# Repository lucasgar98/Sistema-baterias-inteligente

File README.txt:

================================================================================
  SISTEMA INTELIGENTE DE CARGA, DESCARGA Y DIAGNÓSTICO DE BATERÍAS (PROYECTO)
================================================================================

Este proyecto es una plataforma integrada de hardware y software diseñada para 
realizar ciclos de carga, descarga y caracterización de baterías de múltiples 
químicas (Li-Ion, Pb, NiMH). 

El sistema combina el control de potencia en tiempo real (MicroPython), una 
interfaz táctil física (LVGL v8 en CYD), visión por computadora para 
identificación de baterías (ESP32-CAM + pyzbar) y un backend de monitoreo y 
almacenamiento (FastAPI + SQLite + InfluxDB + MQTT) orquestado en Docker.

--------------------------------------------------------------------------------
1. ARQUITECTURA GENERAL Y FLUJO DE DATOS
--------------------------------------------------------------------------------

El flujo de información y control entre los componentes se organiza así:

   [ ESP32-CAM ] -------------( WiFi: Stream MJPEG )-------------> [ FASTAPI ]
         |                                                            |
     ( UART1 )                                                   ( Escribe a DB )
         |                                                            |
         v                                                            v
  [ ESP32 MASTER ]                                            [ SQLITE / INFLUX ]
    |          |
 ( UART2 )   ( I2C / PWM / ADC )
    |          |
    v          v
 [ CYD ]     [ SENSORES (INA219/NTC) y MOSFETS DE POTENCIA ]
 
* Comunicaciones clave:
  - ESP32 Master <-> Cheap Yellow Display (CYD): UART2 a 115200 baudios.
  - ESP32 Master <-> ESP32-CAM: UART1 a 115200 baudios.
  - ESP32 Master -> Sensor de Corriente (INA219): Bus I2C.
  - ESP32 Master -> MOSFETs de potencia: Señal digital PWM.
  - FastAPI (Servidor) <-> Broker MQTT (Mosquitto): Red local TCP.

--------------------------------------------------------------------------------
2. ESTRUCTURA DEL PROYECTO (Workspace)
--------------------------------------------------------------------------------

El repositorio se organiza de la siguiente manera:

/ (Raíz del proyecto)
|-- docker-compose.yml           <- Orquestador de servicios (Mosquitto, InfluxDB, API)
|-- README.txt                   <- Esta documentación principal
|
|-- backend/                     <- Servidor backend y panel de control web
|   |-- main.py                  <- API FastAPI, cliente MQTT, base de datos y lector QR
|   |-- dockerfile               <- Archivo de construcción de imagen Docker
|   |-- baterias.db              <- Base de datos SQLite (se genera sola al arrancar)
|   `-- frontend/                <- Código del dashboard web para PC
|       `-- index.html           <- Panel de monitoreo web interactivo
|
|-- firmware/                    <- Código fuente para los microcontroladores
|   |-- esp32_master/            <- Firmware del ESP32 Principal (MicroPython)
|   |   |-- main.py              # Lógica de potencia, control PWM y lectura de sensores
|   |   |-- config.json.template # Plantilla para configurar datos de red local
|   |   `-- legacy/              # Histórico: código viejo con botones analógicos
|   |       `-- legacy_main_buttons.py
|   |-- pantalla_cyd/            <- Interfaz gráfica táctil (ESP32 CYD con Arduino C++)
|   |   |-- pantalla_cyd.ino     # Inicialización, drivers de pantalla y lazo táctil
|   |   |-- ui.cpp               # Creación manual de pantallas, sliders y callbacks
|   |   `-- ui.h                 # Definición de variables de pantalla
|   |-- espcam/                  <- Cámara de lectura QR (ESP32-CAM con Arduino C++)
|   |   |-- espcam.ino           # Servidor web local de streaming MJPEG
|   |   `-- legacy/              # Histórico: lector de QR local serial
|   |       `-- legacy_serial_qr_reader.txt
|   `-- test_pantalla/           <- Diagnóstico de hardware táctil y colores
|       `-- test_pantalla.ino
|
|-- hardware/                    <- Archivos de diseño físico y circuital
|   |-- pcb_cargador/            <- Proyecto completo de la placa en KiCad
|   |-- ui_design/               <- Proyecto de prototipado original en EEZ Studio
|   |   |-- Lector Bateria.eez-project
|   |   `-- src/                 # Código LVGL exportado originalmente por EEZ
|   `-- 3d_print/                <- Modelos 3D de la carcasa (.3mf)
|
`-- documentacion/               <- Archivos de soporte y estudio
    |-- datasheets/              <- Fichas técnicas en PDF (MOSFETs, integrados)
    |-- BOM/                     <- Listas de materiales (formatos Excel y Word)
    |-- informes/                <- Reportes académicos y bitácora de cambios (PDF)
    `-- videos/                  <- Videos de demostración del circuito (MP4)

--------------------------------------------------------------------------------
3. EXPLICACIÓN DE COMPONENTES
--------------------------------------------------------------------------------

[ ESP32 Master ]
* Lazo de Corriente Constante: Genera PWM a 500 Hz para excitar los gates de los 
  MOSFETs. Aumenta o disminuye el ciclo de trabajo (+/- 20 pasos sobre 1000) 
  dependiendo de si la lectura de corriente está por debajo o por encima del 
  objetivo deseado (ej. 900 mA).
* Corrección de Tensión: Compensa dinámicamente las lecturas del voltaje en 
  función de la caída de tensión introducida por shunts y cables durante la 
  carga (-0.0001V por mA) y descarga (+0.00015V por mA).
* Filtro de Temperatura (EMA): Suaviza las muestras analógicas del NTC usando
  un promedio móvil exponencial con factor alpha = 0.08:
     T_filtrada = 0.08 * T_actual + 0.92 * T_anterior
* Seguridad Térmica: Si la temperatura supera los 45°C, detiene de inmediato 
  las salidas PWM y bloquea la operación. Se restablece automáticamente cuando 
  desciende por debajo de los 40°C.
* Lógica AUTO (Máquina de Estados): Corre la secuencia:
  Descarga inicial -> Espera enfriamiento -> Carga -> Espera -> Descarga de test.

[ Pantalla CYD (Cheap Yellow Display) ]
* Interfaz LVGL v8: Cuenta con navegación deslizable por pestañas (TileView):
  1. Principal: Mediciones en vivo, botones de acción rápida, QR activo.
  2. Parámetros: Selección de químicas y límites de voltaje/corriente.
  3. Red: Conexión WiFi/MQTT on-demand y teclado virtual para configuración.
* Integración UART: La pantalla no toma decisiones de potencia; le envía comandos 
  al Master (ej: "START_C", "SET_LIMITS:c,d,i") y recibe de éste cadenas JSON 
  con la telemetría en tiempo real.

[ ESP32-CAM ]
* Emisor de Video: Expone el stream MJPEG en la ruta http://[IP]/stream a 10 FPS 
  en resolución SVGA (800x600). Solicita datos WiFi al Master por Serial al iniciar.

[ Backend en Servidor (Docker FastAPI) ]
* Servidor y API REST: FastAPI orquesta la comunicación de todo el sistema. Expone 
  los endpoints para la interfaz web, el control remoto y la base de datos SQL.
* Decodificador QR en Servidor: El endpoint "/video_feed" capta el stream de la 
  cámara y aplica un pipeline de mejora de imagen (rotación, escala de grises, 
  contraste 2.0, umbrales de binarización y reescalado 2x) para decodificar el QR 
  con la librería "pyzbar" de forma robusta, previniendo crashes en el ESP32-CAM.
* Guardado de Telemetría: Consume las lecturas vía MQTT y las escribe tanto en 
  InfluxDB (series de tiempo en vivo) como en SQLite (ciclos cerrados y estadísticas).

--------------------------------------------------------------------------------
3.5 DETALLE DE SERVICIOS EN DOCKER Y PERSISTENCIA
--------------------------------------------------------------------------------

La infraestructura del backend se levanta en un entorno virtual aislado mediante 
Docker Compose, configurado en el archivo "docker-compose.yml". Se compone de 
tres servicios clave que cooperan en red:

1. Broker MQTT (Servicio "mosquitto")
   * Imagen: "eclipse-mosquitto:latest"
   * Puertos expuestos:
     - 1884 (externo, para conexión local TCP/IP) -> 1883 (interno de la red Docker)
     - 9001 (interno/externo, para WebSockets en caso de dashboards web directos)
   * Configuración: Carga el archivo "./mosquitto/config/mosquitto.conf". Está 
     configurado para permitir conexiones anónimas ("allow_anonymous true") para 
     simplificar el desarrollo y conexión de los microcontroladores.
   * Temas (Topics) MQTT del sistema:
     - "ESP32/telemetria": Cadenas de texto plano enviadas por el Master cada 3s 
       con formato "v:val,i:val,t:val,s:estado,qr:id,ah:val,p:perfil,vc:val,vd:val".
     - "ESP32/bateria_qr": Intercambio bidireccional del QR de la batería activa.
     - "ESP32/config_perfil": Consignas de límites de carga y descarga ("V_C:x.x,V_D:y.y").
     - "ESP32/comandos": Órdenes de control ("START_C", "START_D", "STOP_ALL").
     - "ESP32/espcam_ip": La cámara publica su IP para descubrimiento automático.
     - "ESP32/alerta_critica": Mensajes de error térmico ("SOBRETEMPERATURA:xxC").
   * Persistencia: Carpeta local "./mosquitto/data" montada en "/mosquitto/data".

2. Base de Datos Temporal (Servicio "influxdb")
   * Imagen: "influxdb:1.8" (versión 1.8 seleccionada por compatibilidad sencilla 
     y consultas HTTP directas sin autenticación por tokens complejos).
   * Puerto expuesto: 8086 (API de consulta y escritura).
   * Base de datos interna: "baterias_db".
   * Estructura de datos: Almacena la medición "telemetria_modulo".
     - Tags (indexados): "qr" (identificador de la batería).
     - Fields: "voltaje" (Float), "corriente" (Float), "temperatura" (Float).
   * Persistencia: Volumen local "./influxdb/data" mapeado a "/var/lib/influxdb" 
     para conservar las mediciones entre reinicios de los contenedores.

3. Servidor de Control y Base de Datos Relacional (Servicio "backend_baterias")
   * Imagen: Construida localmente con el "./backend/dockerfile". Usa Python 3.10-slim 
     e instala las librerías del sistema ("libzbar0" para lectura de QR) y de Python 
     ("fastapi", "uvicorn", "paho-mqtt", "sqlalchemy", "influxdb", "pyzbar", "pillow").
   * Puerto expuesto: 8000 (acceso a la interfaz web y endpoints).
   * Persistencia:
     - Mapea "./backend:/app" para permitir edición de código en vivo sin 
       reconstruir el contenedor.
     - Guarda el archivo de base de datos SQLite en "./backend/baterias.db".
   * Esquema SQLite (ORM SQLAlchemy):
     - Tabla "baterias_inventario" (Registro único de cada batería escaneada).
       Campos: "qr_id" (Texto, clave primaria), "fecha_registro" (Fecha/Hora), 
       "estado_general" (Texto).
     - Tabla "historial_ciclos" (Registro completo de cada carga/descarga terminada).
       Campos: "id" (Entero, auto-incremental), "qr_id" (Texto), "tipo_ciclo" (Texto), 
       "fecha_inicio" (Fecha/Hora), "fecha_fin" (Fecha/Hora), "voltaje_final" (Float), 
       "temp_maxima" (Float), "capacidad_ah" (Float), "soh_porcentaje" (Float), 
       "resistencia_interna" (Float).
   * Cliente MQTT Integrado: Al arrancar el backend en FastAPI, se inicia un hilo 
     secundario con el cliente MQTT ("paho-mqtt") que se suscribe a los tópicos del 
     Master. Éste procesa las tramas, calcula en tiempo real la capacidad acumulada 
     (integración por trapecios respecto al tiempo real) e identifica transiciones 
     de estado (ej. de REPOSO a CARGANDO) para abrir y cerrar ciclos en SQLite.
   * Servidor de Interfaz Web: Monta la carpeta "./backend/frontend" en la ruta 
     HTTP "/web" y sirve la web interactiva [index.html](file:///c:/Gonza/Carrera/Plan%202023/3er%20Año/Digitales%20IV/Proyecto%20bateria/backend/frontend/index.html) en la ruta raíz "/".

--------------------------------------------------------------------------------
4. MAPA DE CONEXIÓN DE PINES (PINOUT)
--------------------------------------------------------------------------------

+--------------------+---------------+---------------------+---------------+-----------------------------------+
| Dispositivo Origen | Pin de Salida | Dispositivo Destino | Pin de Entrada| Descripción / Protocolo           |
+--------------------+---------------+---------------------+---------------+-----------------------------------+
| ESP32 Master       | GPIO 18 (PWM) | MOSFET Canal N      | Gate          | Control de corriente de carga     |
| ESP32 Master       | GPIO 19 (PWM) | MOSFET Canal P      | Gate          | Control de corriente de descarga   |
| ESP32 Master       | GPIO 33 (ADC) | Divisor de Voltaje  | V_BAT         | Medición de voltaje de batería    |
| ESP32 Master       | GPIO 34 (ADC) | Divisor NTC         | Temperatura   | Medición de temperatura NTC       |
| ESP32 Master       | GPIO 21       | Sensor INA219       | SDA           | Bus I2C - Datos de corriente      |
| ESP32 Master       | GPIO 22       | Sensor INA219       | SCL           | Bus I2C - Reloj de corriente      |
| ESP32 Master       | GPIO 27 (TX1) | ESP32-CAM           | RX (U0R)      | UART1 - Envío configuración WiFi  |
| ESP32 Master       | GPIO 26 (RX1) | ESP32-CAM           | TX (U0T)      | UART1 - Recepción IP de cámara    |
| ESP32 Master       | GPIO 17 (TX2) | Pantalla CYD (CN1)  | RX (GPIO 22)  | UART2 - Transmisión de telemetría |
| ESP32 Master       | GPIO 16 (RX2) | Pantalla CYD (CN1)  | TX (GPIO 27)  | UART2 - Recepción de comandos     |
+--------------------+---------------+---------------------+---------------+-----------------------------------+

--------------------------------------------------------------------------------
5. GUÍA DE DESPLIEGUE Y PUESTA EN MARCHA
--------------------------------------------------------------------------------

A. Iniciar Infraestructura de Servidor (PC de laboratorio con Docker instalado):
   1. Colocarse en la raíz del proyecto (donde está "docker-compose.yml").
   2. Ejecutar el comando en la terminal:
         docker compose up --build -d
   3. Ingresar en el navegador web a: http://localhost:8000 para abrir la app.

B. Preparar ESP32 Master:
   1. Flashear la placa con MicroPython estable (v1.20 o superior).
   2. Subir el archivo de control "firmware/esp32_master/main.py".
   3. Copiar el archivo "config.json.template", renombrarlo como "config.json", 
      completar las credenciales WiFi y de MQTT de tu red y subirlo.
   4. Subir las librerías "ina219.py" y "umqtt/simple.py" a la placa.

C. Cargar Firmware de CYD y Cámara (Arduino IDE):
   * Pantalla CYD: Abrir "firmware/pantalla_cyd/pantalla_cyd.ino". 
     Librerías necesarias: "lvgl" (v8.x), "TFT_eSPI" (configurada con driver 
     y pines para la CYD), "XPT2046_Touchscreen" y "ArduinoJson".
   * ESP32-CAM: Abrir "firmware/espcam/espcam.ino". 
     Flashear seleccionando placa "AI Thinker ESP32-CAM".

--------------------------------------------------------------------------------
6. RESUMEN DE CAMBIOS REALIZADOS
--------------------------------------------------------------------------------

* Migración de Control Físico a Digital: Se removieron botones cableados en favor 
  de comandos por puerto serie desde la pantalla táctil.
* Procesamiento de QR en Servidor: Lector de QR se delegó al backend FastAPI 
  para evitar sobrecalentamientos y crashes en el ESP32-CAM.
* Módulos de Cálculo: Se añadió la estimación de Resistencia Interna (RI) 
  y el Porcentaje de Salud (SoH).
* Organización Limpia: Se clasificaron todos los archivos del repositorio en 
  firmware, hardware y documentación, dejando la raíz despejada y ordenada.
================================================================================

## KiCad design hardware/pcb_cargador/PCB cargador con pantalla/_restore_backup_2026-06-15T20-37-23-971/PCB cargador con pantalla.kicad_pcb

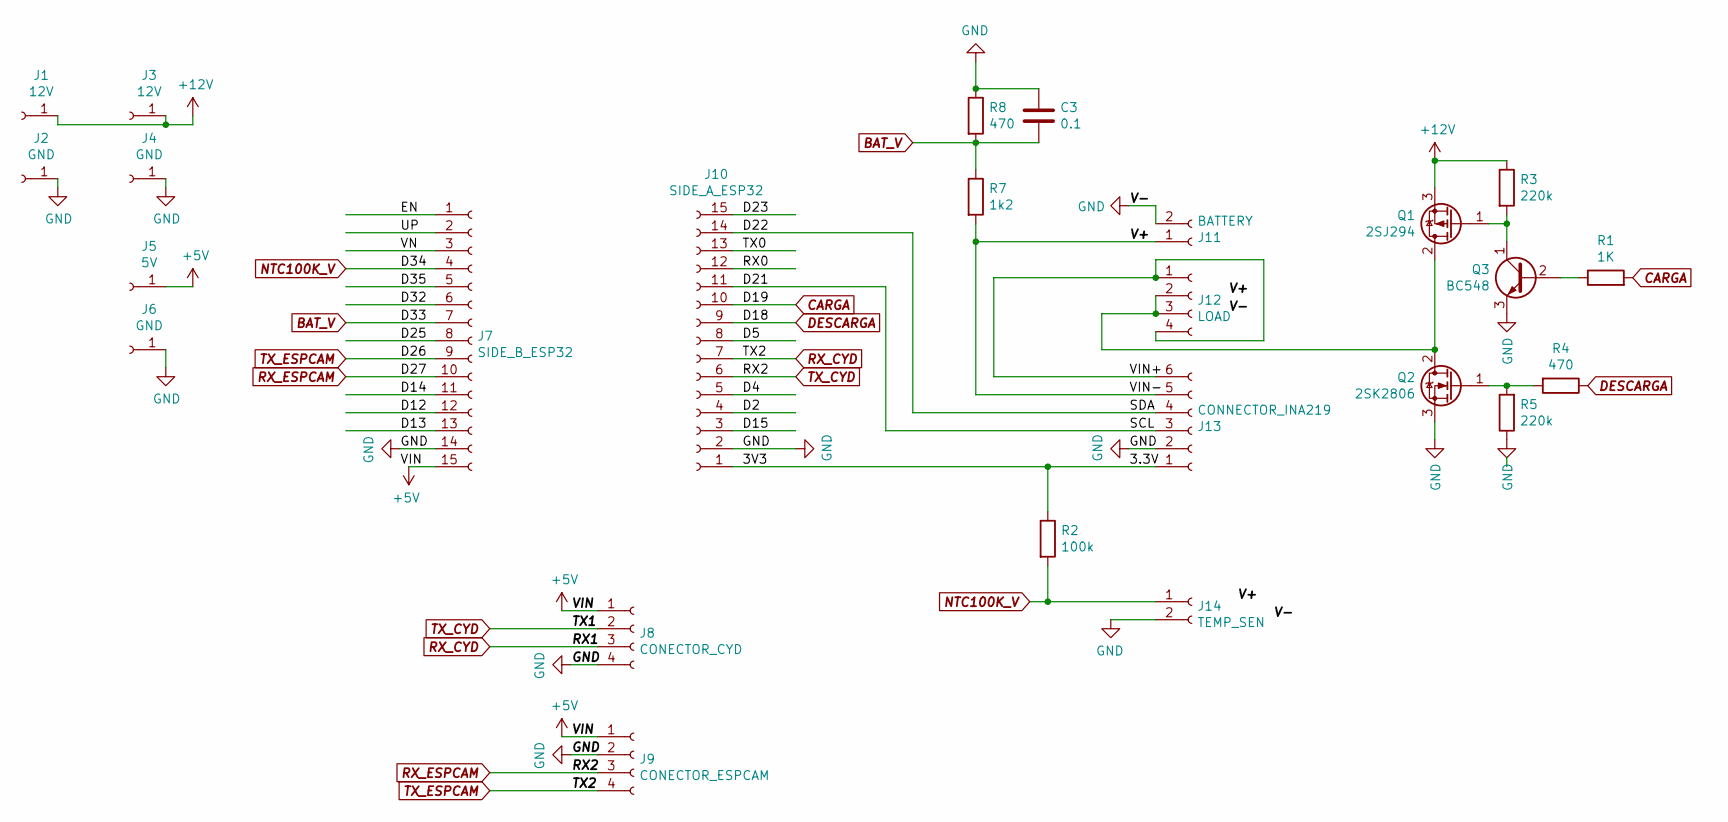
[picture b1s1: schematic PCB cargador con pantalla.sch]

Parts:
C3: 0.1; C_Disc_D5.0mm_W2.5mm_P2.50mm
J1, J3: 12V; PinHeader_1x01_P2.54mm_Vertical
J2, J4, J6: GND; PinHeader_1x01_P2.54mm_Vertical
J5: 5V; PinHeader_1x01_P2.54mm_Vertical
J7: SIDE_B_ESP32; PinHeader_1x15_P2.54mm_Vertical
J8: CONECTOR_CYD; PinHeader_1x04_P2.54mm_Vertical
J9: CONECTOR_ESPCAM; PinHeader_1x04_P2.54mm_Vertical
J10: SIDE_A_ESP32; PinHeader_1x15_P2.54mm_Vertical
J11: BATTERY; PinHeader_1x02_P2.54mm_Vertical
J12: LOAD; PinHeader_1x04_P2.54mm_Vertical
J13: CONNECTOR_INA219; PinHeader_1x06_P2.54mm_Vertical
J14: TEMP_SEN; PinHeader_1x02_P2.54mm_Vertical
Q1: 2SJ294; TO-220F-3_Vertical
Q2: 2SK2806; TO-220-3_Vertical
Q3: BC548; TO-92L_Inline_Wide
R1: 1K; R_Axial_DIN0207_L6.3mm_D2.5mm_P10.16mm_Horizontal
R2: 100k; R_Axial_DIN0207_L6.3mm_D2.5mm_P10.16mm_Horizontal
R3, R5: 220k; R_Axial_DIN0207_L6.3mm_D2.5mm_P10.16mm_Horizontal
R4, R8: 470; R_Axial_DIN0207_L6.3mm_D2.5mm_P10.16mm_Horizontal
R7: 1k2; R_Axial_DIN0207_L6.3mm_D2.5mm_P10.16mm_Horizontal

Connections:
+5V: J5.1, J7.15, J8.1, J9.1
+12V: J1.1, J3.1, Q1.3 (S), R3.1
/3.3V: J10.1, J13.1, R2.1
/D2: J10.4
/D4: J10.5
/D5: J10.8
/D12: J7.12
/D13: J7.13
/D14: J7.11
/D15: J10.3
/D21: J10.11, J13.3
/D22: J10.14, J13.4
/D23: J10.15
/D25: J7.8
/D32: J7.6
/D35: J7.5
/EN: J7.1
/RX0: J10.12
/TX0: J10.13
/UP: J7.2
/V+: J11.1, J13.5, R7.2
/VIN+: J12.1, J12.4, J13.6
/VN: J7.3
BAT_V: C3.2, J7.7, R7.1, R8.2
CARGA: J10.10, R1.2
DESCARGA: J10.9, R4.1
GND: C3.1, J2.1, J4.1, J6.1, J7.14, J8.4, J9.2, J10.2, J11.2, J13.2, J14.2, Q2.3 (S), Q3.3 (E), R5.1, R8.1
NTC100K_V: J7.4, J14.1, R2.2
unnamed: J12.2, J12.3, Q1.2 (D), Q2.2 (D)
unnamed: Q1.1 (G), Q3.1 (C), R3.2
unnamed: Q2.1 (G), R4.2, R5.2
unnamed: Q3.2 (B), R1.1
RX_CYD: J7.9, J8.3, J9.4, J10.7
RX_ESPCAM: J7.10, J8.2, J9.3, J10.6

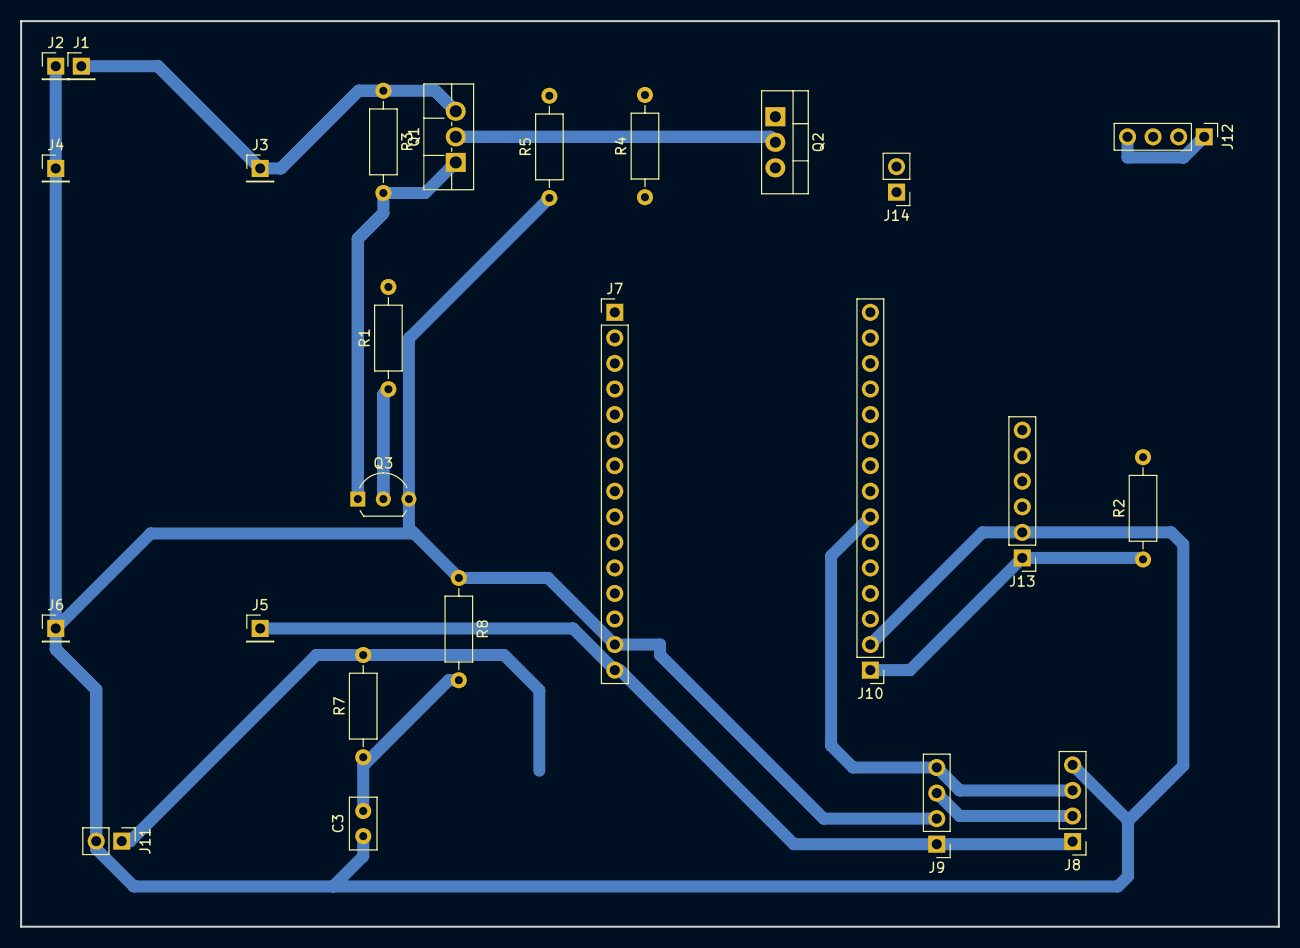
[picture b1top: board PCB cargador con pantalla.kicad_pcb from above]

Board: 2 copper layers, 125.0 x 90.0 mm, 25 parts (0 on the bottom side), 18 nets.
